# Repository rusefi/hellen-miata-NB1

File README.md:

# Hellen NB1 Miata

Issues are tracked publicly at https://github.com/rusefi/hellen-NB1-issues

[User Documentation](https://github.com/rusefi/rusefi/wiki/Hellen-NB1)

https://docs.google.com/spreadsheets/d/19Mc_QA4MTJAY1hUR4UMexbdGiqNpH4JARKxWm1VD5KA

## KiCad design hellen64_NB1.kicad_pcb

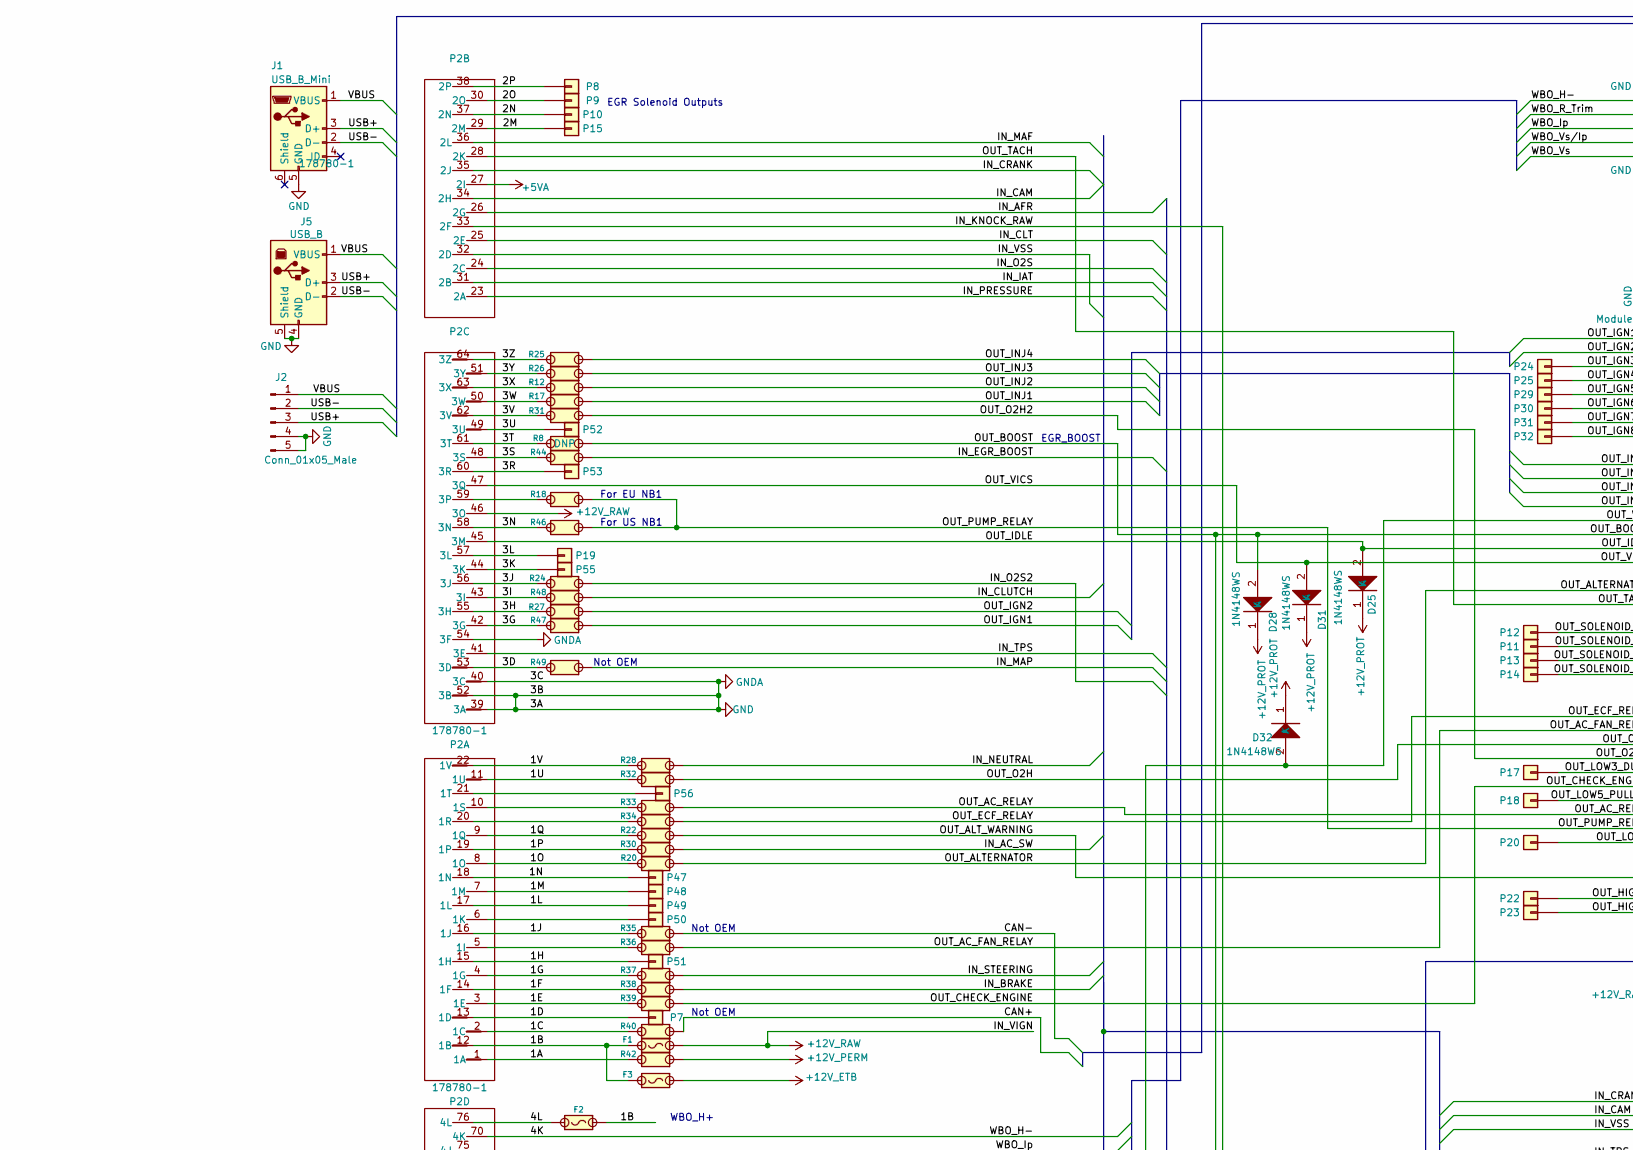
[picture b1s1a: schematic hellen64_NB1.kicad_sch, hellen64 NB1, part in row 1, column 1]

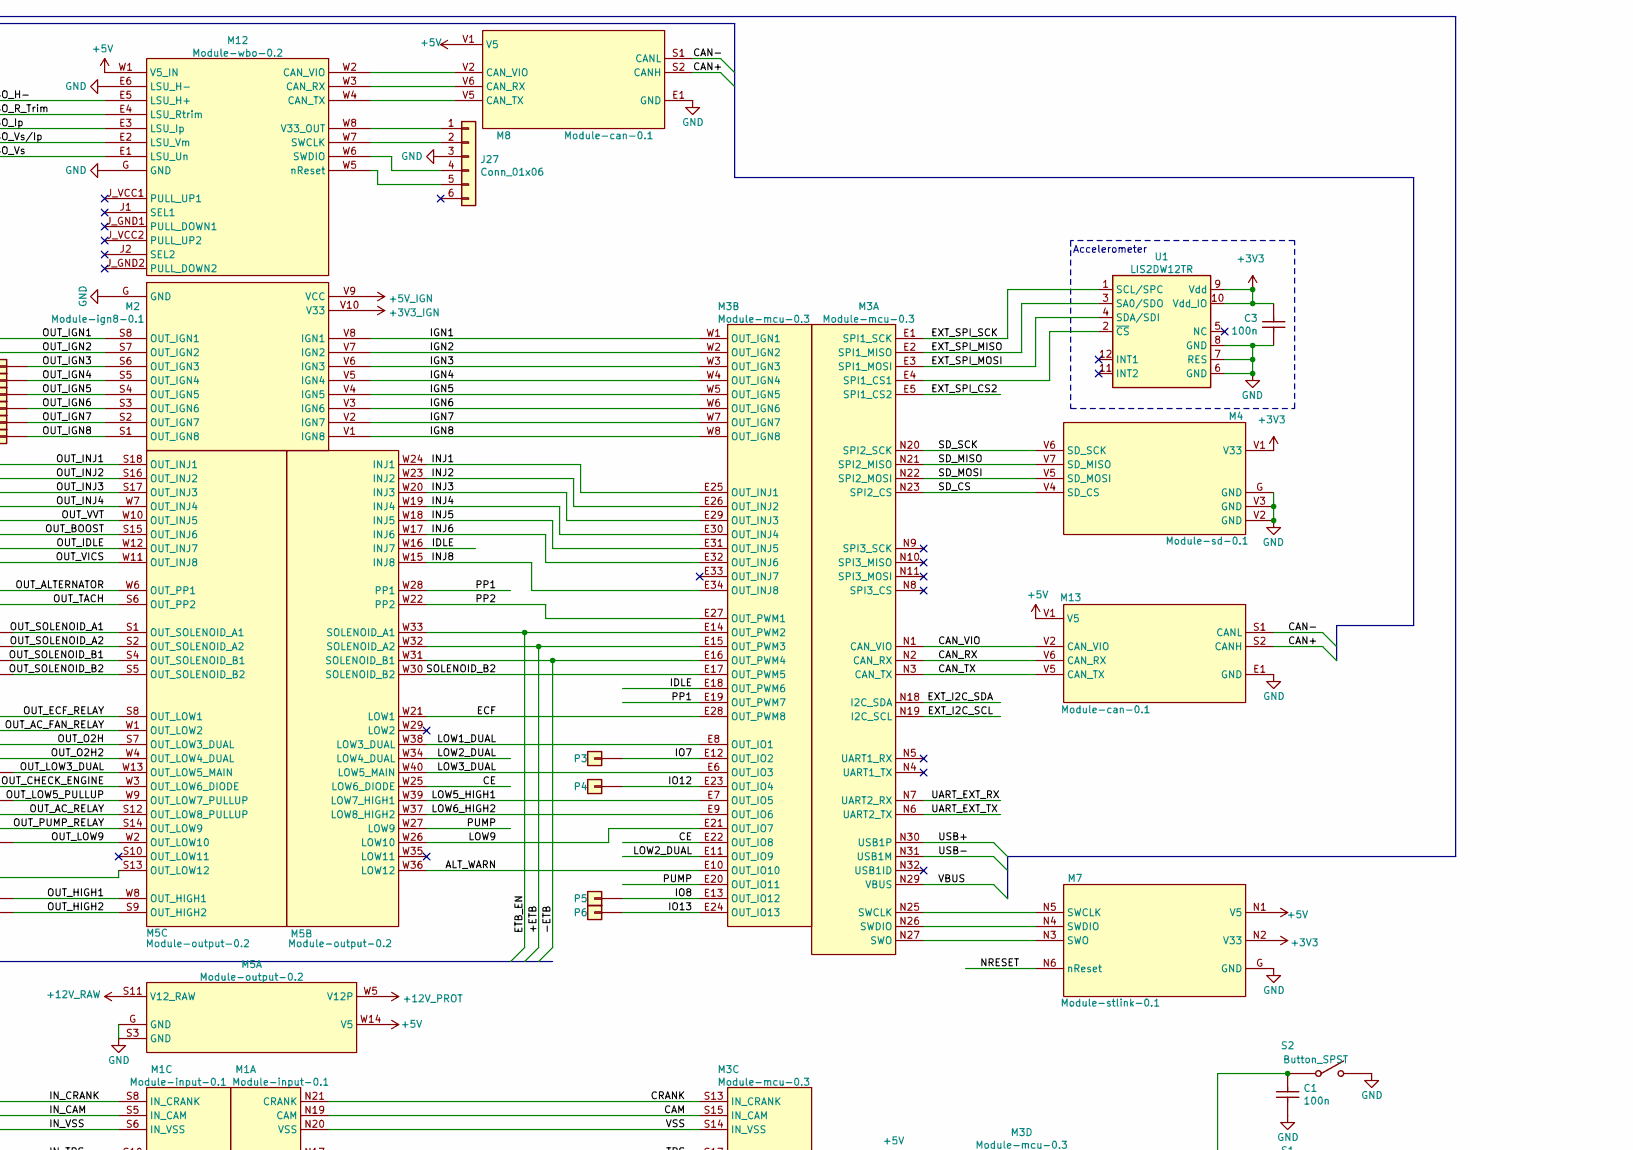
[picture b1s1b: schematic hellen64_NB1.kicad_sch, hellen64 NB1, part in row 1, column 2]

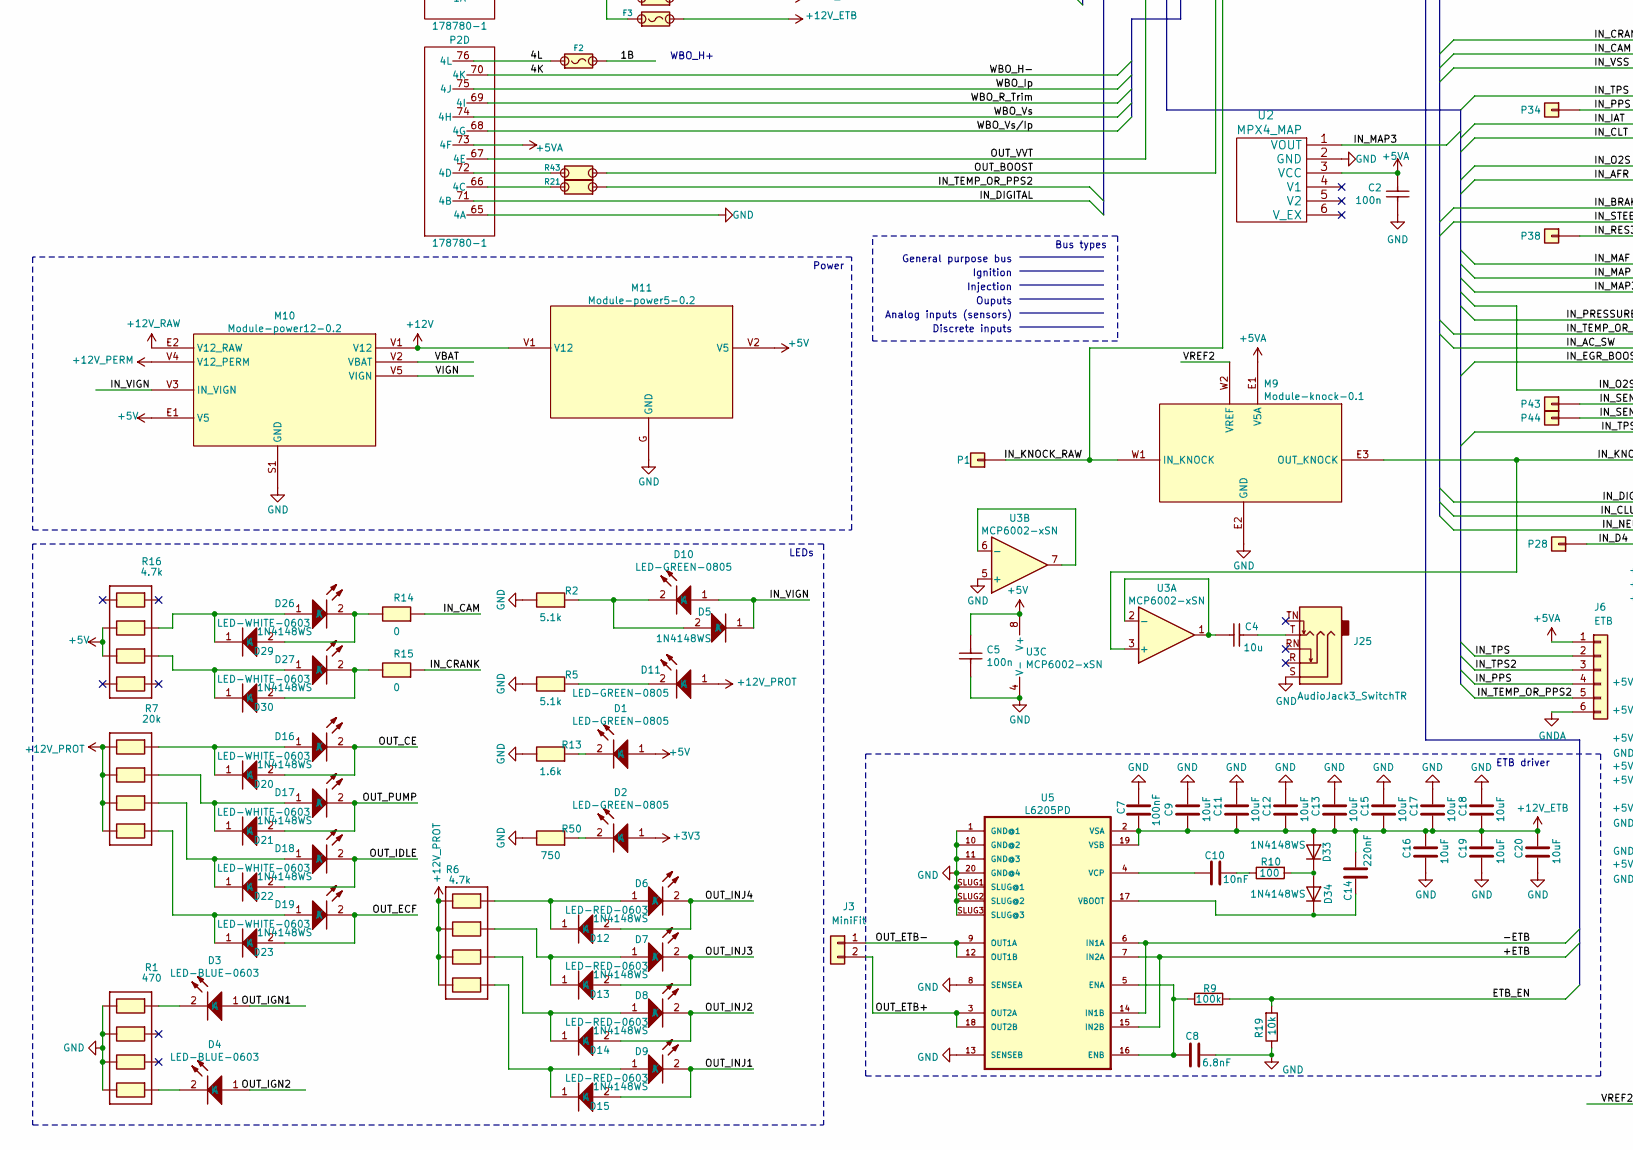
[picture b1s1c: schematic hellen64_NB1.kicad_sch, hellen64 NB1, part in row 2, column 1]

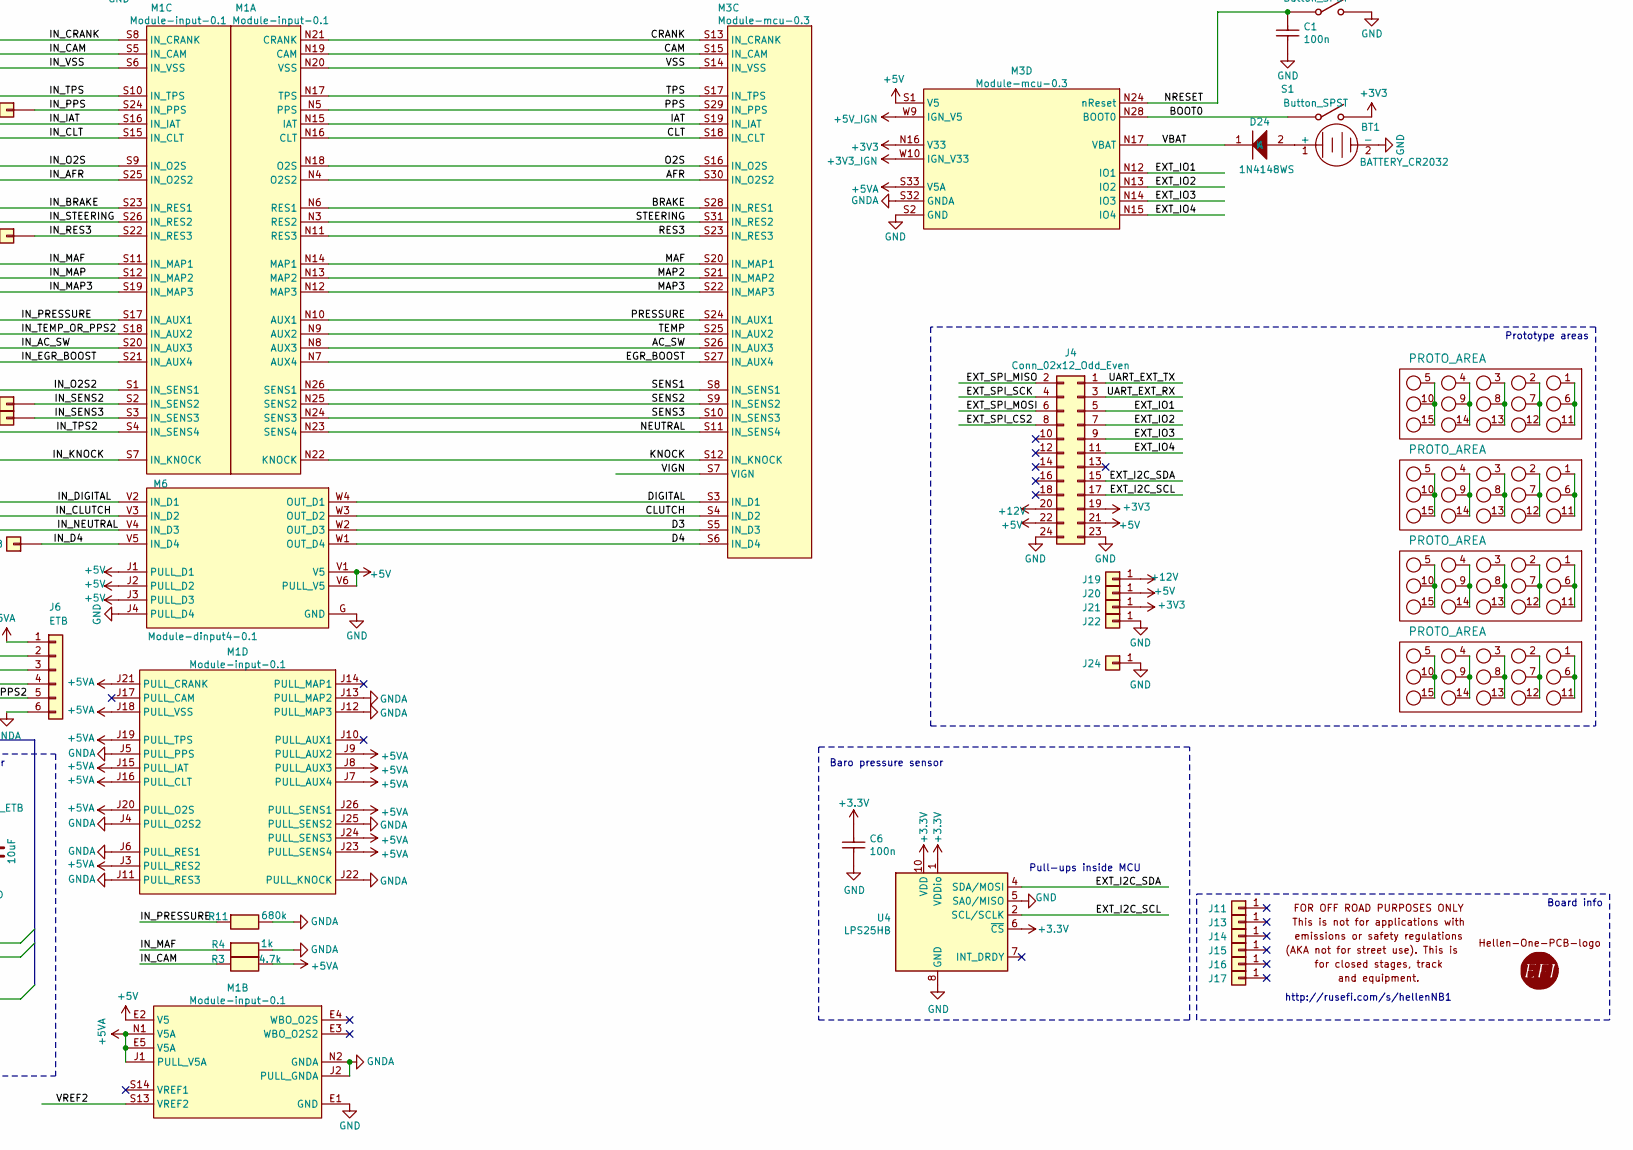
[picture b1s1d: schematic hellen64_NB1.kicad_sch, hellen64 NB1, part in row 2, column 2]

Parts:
BT1: BATTERY_CR2032; BatteryHolder_Keystone_1060_1x2032; LCSC C70377
C1, C2, C3, C5, C6: 100n; C0603; LCSC C14663
C4: 10u; C0603; LCSC C19702
C7: 100nF; C0603; LCSC C14663
C8: 6.8nF; C0603; LCSC C1631
C9, C11, C12, C13, C15, C16, C17, C18, C19, C20: 10uF; C0805; LCSC C15850
C10: 10nF; C0603; LCSC C57112
C14: 220nF; C0603; LCSC C21120
D1, D2, D10, D11: LED-GREEN-0805; LED-0805; LCSC C2297
D3, D4: LED-BLUE-0603; LED-0603; LCSC C72041
D5, D12, D13, D14, D15, D20, D21, D22, D23, D24, D25, D28, D29, D30, D31, D32, D33, D34: 1N4148WS; SOD-323; LCSC C2128
D6, D7, D8, D9: LED-RED-0603; LED-0603; LCSC C2286
D16, D17, D18, D19, D26, D27: LED-WHITE-0603; LED-0603; LCSC C2290
F1, F2, F3: Fuse-Pad-Pad; PAD-1206-PAD; LCSC C182446
G1, G3: LOGO
G2: DISCLAIMER; Off_Road_Disclaimer
G4, G5, G6, G7: PROTO_AREA
J1: USB_B_Mini; USB-MINI-B-VERTICAL; LCSC C13453
J2: Conn_01x05_Male; Molex_SPOX_5267-05A_1x05_P2.50mm_Vertical
J3: MiniFit; Molex-39301020; LCSC C240832
J4: Conn_02x12_Odd_Even; PinHeader_2x12_P2.54mm_Vertical
J5: USB_B; LCSC C46392
J6: ETB; PinHeader_1x06_P2.54mm_Vertical; LCSC C343639
J11, J13, J14, J15, J16, J17: Conn_01x01; MountingHole_4.5mm_Pad
J19, J20, J21, J22, J24: Conn_01x01; TestPoint_Pad_D2.0mm
J25: AudioJack3_SwitchTR; Jack_3.5mm_PJ-3250-5A; LCSC C165947
J27: Conn_01x06; PinHeader_1x06_P2.54mm_Vertical
M1: Module-input-0.1; input
M2: Module-ign8-0.1; ign8
M3: Module-mcu-0.3; mcu
M4: Module-sd-0.1; sd
M5: Module-output-0.2; output
M6: Module-dinput4-0.1; dinput4
M7: Module-stlink-0.1; stlink
M8, M13: Module-can-0.1; can
M9: Module-knock-0.1; knock
M10: Module-power12-0.2; power12
M11: Module-power5-0.2; power5
M12: Module-wbo-0.2; wbo
P1, P3, P4, P5, P6, P7, P8, P9, P10, P11, P12, P13, P14, P15, P17, P18, P19, P20, P22, P23, P24, P25, P28, P29, P30, P31, P32, P34, P38, P43, P44, P47, P48, P49, P50, P51, P52, P53, P55, P56: Pad; PAD-TH
P2: 178780-1
R1: 470; R0603-4; LCSC C25510
R2, R5: 5.1k; R0603; LCSC C23186
R3: 4.7k; R0603; LCSC C23162
R4: 1k; R0603; LCSC C21190
R6, R16: 4.7k; R0603-4; LCSC C1980
R7: 20k; R0603-4; LCSC C12004
R8: Jumper-Pad-Pad; PAD-0805-PAD
R9: 100k; R0603; LCSC C25803
R10: 100; R0603; LCSC C22775
R11: 680k; R0603; LCSC C25822
R12, R17, R18, R20, R21, R22, R24, R25, R26, R27, R28, R30, R31, R32, R33, R34, R35, R36, R37, R38, R39, R40, R42, R43, R44, R46, R47, R48, R49: Jumper-Pad-Pad; PAD-0805-PAD; LCSC C17477
R13: 1.6k; R0603; LCSC C22847
R14, R15: 0; R0603; LCSC C21189
R19: 10k; R0603; LCSC C25804
R50: 750; R0603; LCSC C23241
S1, S2: Button_SPST; SMD-2_2.9x3.9x1.7; LCSC C115357
U1: LIS2DW12TR; LGA-12_2x2mm_P0.5mm; LCSC C189624
U2: MPX4_MAP; MPX-4_MAP
U3: MCP6002-xSN; SOIC-8_3.9x4.9mm_P1.27mm; LCSC C7377
U4: LPS25HB; ST_HLGA-10_2.5x2.5mm_P0.6mm_LayoutBorder3x2y; LCSC C87898
U5: L6205PD; SO20POWER; LCSC C36543

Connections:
+3V3_IGN: M2.V10 (V33), M3.W10 (IGN_V33)
+5V: C5.2, D1.1 (A), J4.21, J4.22, J20.1, M1.E2 (V5), M3.S1 (V5), M5.W14 (V5), M6.J1 (PULL_D1), M6.J2 (PULL_D2), M6.J3 (PULL_D3), M6.V1 (V5), M6.V6 (PULL_V5), M7.N1 (V5), M8.V1 (V5), M10.E1 (V5), M11.V2 (V5), M12.W1 (V5_IN), M13.V1 (V5), R16.2, R16.3, U3.8 (V+)
+5VA: C2.2, J6.1, M1.E5 (V5A), M1.J1 (PULL_V5A), M1.J3 (PULL_RES2), M1.J7 (PULL_AUX4), M1.J8 (PULL_AUX3), M1.J9 (PULL_AUX2), M1.J15 (PULL_IAT), M1.J16 (PULL_CLT), M1.J18 (PULL_VSS), M1.J19 (PULL_TPS), M1.J20 (PULL_O2S), M1.J21 (PULL_CRANK), M1.J23 (PULL_SENS4), M1.J24 (PULL_SENS3), M1.J26 (PULL_SENS1), M1.N1 (V5A), M3.S33 (V5A), M9.E1 (V5A), P2.27 (2I), P2.73 (4F), R3.1, U2.3 (VCC)
+5V_IGN: M2.V9 (VCC), M3.W9 (IGN_V5)
+12V: J4.20, J19.1, M10.V1 (V12), M11.V1 (V12)
+12V_ETB: C7.2, C9.1, C11.1, C12.1, C13.1, C14.1, C15.1, C16.2, C17.1, C18.1, C19.2, C20.2, D33.2 (A), F3.2, U5.2 (VSA), U5.19 (VSB)
+12V_PERM: M10.V4 (V12_PERM), R42.1
+12V_PROT: D11.1 (A), D25.1 (K), D28.1 (K), D31.1 (K), D32.1 (K), M5.W5 (V12P), R6.1, R6.2, R6.3, R6.4, R7.1, R7.2, R7.3, R7.4
+12V_RAW: D5.1 (K), D10.1 (A), F1.2, M5.S11 (V12_RAW), M10.E2 (V12_RAW), M10.V3 (IN_VIGN), P2.46 (3O)
/1A: P2.1 (1A), R42.2
/1B: F1.1, F2.2, F3.1, P2.12 (1B)
/1C: P2.2 (1C), R40.2
/1D: P2.13 (1D), P7.1
/1E: P2.3 (1E), R39.2
/1F: P2.14 (1F), R38.2
/1G: P2.4 (1G), R37.2
/1H: P2.15 (1H), P51.1
/1J: P2.16 (1J), R35.2
/1L: P2.17 (1L), P49.1
/1M: P2.7 (1M), P48.1
/1N: P2.18 (1N), P47.1
/1O: P2.8 (1O), R20.2
/1P: P2.19 (1P), R30.2
/1Q: P2.9 (1Q), R22.2
/1U: P2.11 (1U), R32.2
/1V: P2.22 (1V), R28.2
/2M: P2.29 (2M), P15.1
/2N: P2.37 (2N), P10.1
/2O: P2.30 (2O), P9.1
/2P: P2.38 (2P), P8.1
/3D: P2.53 (3D), R49.2
/3G: P2.42 (3G), R47.2
/3H: P2.55 (3H), R27.1
/3I: P2.43 (3I), R48.2
/3J: P2.56 (3J), R24.2
/3K: P2.44 (3K), P55.1
/3L: P2.57 (3L), P19.1
/3N: P2.58 (3N), R46.2
/3R: P2.60 (3R), P53.1
/3S: P2.48 (3S), R44.2
/3T: P2.61 (3T), R8.2
/3U: P2.49 (3U), P52.1
/3V: P2.62 (3V), R31.2
/3W: P2.50 (3W), R17.1
/3X: P2.63 (3X), R12.1
/3Y: P2.51 (3Y), R26.2
/3Z: P2.64 (3Z), R25.2
/4K: M12.E5 (LSU_H+), P2.70 (4K)
/4L: F2.1, P2.76 (4L)
/+ETB: M3.E15 (OUT_PWM3), M5.W32 (SOLENOID_A2), U5.7 (IN2A), U5.15 (IN2B)
/-ETB: M3.E16 (OUT_PWM4), M5.W31 (SOLENOID_B1), U5.6 (IN1A), U5.14 (IN1B)
/AC_SW: M1.N8 (AUX3), M3.S26 (IN_AUX3)
/AFR: M1.N4 (O2S2), M3.S30 (IN_O2S2)
/ALT_WARN: M3.E10 (OUT_IO10), M5.W36 (LOW12)
/BOOT0: M3.N28 (BOOT0), S1.1
/BRAKE: M1.N6 (RES1), M3.S28 (IN_RES1)
/CAM: M1.N19 (CAM), M3.S15 (IN_CAM)
/CAN+: M8.S2 (CANH), M13.S2 (CANH), R40.1
/CAN-: M8.S1 (CANL), M13.S1 (CANL), R35.1
/CAN_RX: M3.N2 (CAN_RX), M13.V6 (CAN_RX)
/CAN_TX: M3.N3 (CAN_TX), M13.V5 (CAN_TX)
/CAN_VIO: M3.N1 (CAN_VIO), M13.V2 (CAN_VIO)
/CE: M3.E22 (OUT_IO8), M5.W25 (LOW6_DIODE)
/CLT: M1.N16 (CLT), M3.S18 (IN_CLT)
/CLUTCH: M3.S4 (IN_D2), M6.W3 (OUT_D2)
/CRANK: M1.N21 (CRANK), M3.S13 (IN_CRANK)
/D3: M3.S5 (IN_D3), M6.W2 (OUT_D3)
/D4: M3.S6 (IN_D4), M6.W1 (OUT_D4)
/DIGITAL: M3.S3 (IN_D1), M6.W4 (OUT_D1)
/ECF: M3.E28 (OUT_PWM8), M5.W21 (LOW1)
/EGR_BOOST: M1.N7 (AUX4), M3.S27 (IN_AUX4)
/ETB_EN: M3.E14 (OUT_PWM2), M5.W33 (SOLENOID_A1), R9.2, R19.2
/EXT_I2C_SCL: J4.17, M3.N19 (I2C_SCL), U4.2 (SCL/SCLK)
/EXT_I2C_SDA: J4.15, M3.N18 (I2C_SDA), U4.4 (SDA/MOSI)
/EXT_IO1: J4.5, M3.N12 (IO1)
/EXT_IO2: J4.7, M3.N13 (IO2)
/EXT_IO3: J4.9, M3.N14 (IO3)
/EXT_IO4: J4.11, M3.N15 (IO4)
/EXT_SPI_CS2: J4.8, M3.E5 (SPI1_CS2)
/EXT_SPI_MISO: J4.2, M3.E2 (SPI1_MISO), U1.3 (SA0/SDO)
/EXT_SPI_MOSI: J4.6, M3.E3 (SPI1_MOSI), U1.4 (SDA/SDI)
/EXT_SPI_SCK: J4.4, M3.E1 (SPI1_SCK), U1.1 (SCL/SPC)
/IAT: M1.N15 (IAT), M3.S19 (IN_IAT)
/IDLE: M3.E18 (OUT_PWM6), M5.W16 (INJ7)
/IGN1: M2.V8 (IGN1), M3.W1 (OUT_IGN1)
/IGN2: M2.V7 (IGN2), M3.W2 (OUT_IGN2)
/IGN3: M2.V6 (IGN3), M3.W3 (OUT_IGN3)
/IGN4: M2.V5 (IGN4), M3.W4 (OUT_IGN4)
/IGN5: M2.V4 (IGN5), M3.W5 (OUT_IGN5)
/IGN6: M2.V3 (IGN6), M3.W6 (OUT_IGN6)
/IGN7: M2.V2 (IGN7), M3.W7 (OUT_IGN7)
/IGN8: M2.V1 (IGN8), M3.W8 (OUT_IGN8)
/INJ1: M3.E25 (OUT_INJ1), M5.W24 (INJ1)
/INJ2: M3.E26 (OUT_INJ2), M5.W23 (INJ2)
/INJ3: M3.E29 (OUT_INJ3), M5.W20 (INJ3)
/INJ4: M3.E30 (OUT_INJ4), M5.W19 (INJ4)
/INJ5: M3.E31 (OUT_INJ5), M5.W18 (INJ5)
/INJ6: M3.E32 (OUT_INJ6), M5.W17 (INJ6)
/INJ8: M3.E34 (OUT_INJ8), M5.W15 (INJ8)
/IN_AC_SW: M1.S20 (IN_AUX3), R30.1
/IN_AFR: M1.S25 (IN_O2S2), P2.26 (2G)
/IN_BRAKE: M1.S23 (IN_RES1), R38.1
/IN_CAM: M1.S5 (IN_CAM), P2.34 (2H), R3.2, R14.1
/IN_CLT: M1.S15 (IN_CLT), P2.25 (2E)
/IN_CLUTCH: M6.V3 (IN_D2), R48.1
/IN_CRANK: M1.S8 (IN_CRANK), P2.35 (2J), R15.1
/IN_D4: M6.V5 (IN_D4), P28.1
/IN_DIGITAL: M6.V2 (IN_D1), P2.71 (4B)
/IN_EGR_BOOST: M1.S21 (IN_AUX4), R44.1
/IN_IAT: M1.S16 (IN_IAT), P2.31 (2B)
/IN_KNOCK: M1.S7 (IN_KNOCK), M9.E3 (OUT_KNOCK), U3.3 (+)
/IN_KNOCK_RAW: M9.W1 (IN_KNOCK), P1.1, P2.33 (2F)
/IN_MAF: M1.S11 (IN_MAP1), P2.36 (2L), R4.1
/IN_MAP: M1.S12 (IN_MAP2), R49.1
/IN_MAP3: M1.S19 (IN_MAP3), U2.1 (VOUT)
/IN_NEUTRAL: M6.V4 (IN_D3), R28.1
/IN_O2S: M1.S9 (IN_O2S), P2.24 (2C)
/IN_O2S2: M1.S1 (IN_SENS1), R24.1
/IN_PPS: J6.4, M1.S24 (IN_PPS), P34.1
/IN_PRESSURE: M1.S17 (IN_AUX1), P2.23 (2A), R11.1
/IN_RES3: M1.S22 (IN_RES3), P38.1
/IN_SENS2: M1.S2 (IN_SENS2), P43.1
/IN_SENS3: M1.S3 (IN_SENS3), P44.1
/IN_STEERING: M1.S26 (IN_RES2), R37.1
/IN_TEMP_OR_PPS2: J6.5, M1.S18 (IN_AUX2), R21.1
/IN_TPS: J6.2, M1.S10 (IN_TPS), P2.41 (3E)
/IN_TPS2: J6.3, M1.S4 (IN_SENS4)
/IN_VSS: M1.S6 (IN_VSS), P2.32 (2D)
/IO7: M3.E12 (OUT_IO2), P3.1
/IO8: M3.E13 (OUT_IO12), P5.1
/IO12: M3.E23 (OUT_IO4), P4.1
/IO13: M3.E24 (OUT_IO13), P6.1
/KNOCK: M1.N22 (KNOCK), M3.S12 (IN_KNOCK)
/LOW1_DUAL: M3.E8 (OUT_IO1), M5.W38 (LOW3_DUAL)
/LOW2_DUAL: M3.E11 (OUT_IO9), M5.W34 (LOW4_DUAL)
/LOW3_DUAL: M3.E6 (OUT_IO3), M5.W40 (LOW5_MAIN)
/LOW5_HIGH1: M3.E7 (OUT_IO5), M5.W39 (LOW7_HIGH1)
/LOW6_HIGH2: M3.E9 (OUT_IO6), M5.W37 (LOW8_HIGH2)
/LOW9: M3.E21 (OUT_IO7), M5.W26 (LOW10)
/MAF: M1.N14 (MAP1), M3.S20 (IN_MAP1)
/MAP2: M1.N13 (MAP2), M3.S21 (IN_MAP2)
/MAP3: M1.N12 (MAP3), M3.S22 (IN_MAP3)
/NEUTRAL: M1.N23 (SENS4), M3.S11 (IN_SENS4)
/NRESET: C1.2, M3.N24 (nReset), M7.N6 (nReset), S2.1
/O2S: M1.N18 (O2S), M3.S16 (IN_O2S)
/OUT_AC_FAN_RELAY: M5.W1 (OUT_LOW2), R36.1
/OUT_AC_RELAY: M5.S12 (OUT_LOW8_PULLUP), R33.1
/OUT_ALTERNATOR: M5.W6 (OUT_PP1), R20.1
/OUT_ALT_WARNING: M5.S13 (OUT_LOW12), R22.1
/OUT_BOOST: D28.2 (A), M5.S15 (OUT_INJ6), R8.1, R43.1
/OUT_CE: D16.2 (K), D20.2 (A)
/OUT_CHECK_ENGINE: M5.W3 (OUT_LOW6_DIODE), R39.1
/OUT_ECF: D19.2 (K), D23.2 (A)
/OUT_ECF_RELAY: M5.S8 (OUT_LOW1), R34.1
/OUT_ETB+: J3.2, U5.3 (OUT2A), U5.18 (OUT2B)
/OUT_ETB-: J3.1, U5.9 (OUT1A), U5.12 (OUT1B)
/OUT_HIGH1: M5.W8 (OUT_HIGH1), P22.1
/OUT_HIGH2: M5.S9 (OUT_HIGH2), P23.1
/OUT_IDLE: D18.2 (K), D22.2 (A), D25.2 (A), M5.W12 (OUT_INJ7), P2.45 (3M)
/OUT_IGN1: D3.1 (A), M2.S8 (OUT_IGN1), R47.1
/OUT_IGN2: D4.1 (A), M2.S7 (OUT_IGN2), R27.2
/OUT_IGN3: M2.S6 (OUT_IGN3), P24.1
/OUT_IGN4: M2.S5 (OUT_IGN4), P25.1
/OUT_IGN5: M2.S4 (OUT_IGN5), P29.1
/OUT_IGN6: M2.S3 (OUT_IGN6), P30.1
/OUT_IGN7: M2.S2 (OUT_IGN7), P31.1
/OUT_IGN8: M2.S1 (OUT_IGN8), P32.1
/OUT_INJ1: D9.2 (K), D15.2 (A), M5.S18 (OUT_INJ1), R17.2
/OUT_INJ2: D8.2 (K), D14.2 (A), M5.S16 (OUT_INJ2), R12.2
/OUT_INJ3: D7.2 (K), D13.2 (A), M5.S17 (OUT_INJ3), R26.1
/OUT_INJ4: D6.2 (K), D12.2 (A), M5.W7 (OUT_INJ4), R25.1
/OUT_LOW3_DUAL: M5.W13 (OUT_LOW5_MAIN), P17.1
/OUT_LOW5_PULLUP: M5.W9 (OUT_LOW7_PULLUP), P18.1
/OUT_LOW9: M5.W2 (OUT_LOW10), P20.1
/OUT_O2H: M5.S7 (OUT_LOW3_DUAL), R32.1
/OUT_O2H2: M5.W4 (OUT_LOW4_DUAL), R31.1
/OUT_PUMP: D17.2 (K), D21.2 (A)
/OUT_PUMP_RELAY: M5.S14 (OUT_LOW9), R18.1, R46.1
/OUT_SOLENOID_A1: M5.S1 (OUT_SOLENOID_A1), P12.1
/OUT_SOLENOID_A2: M5.S2 (OUT_SOLENOID_A2), P11.1
/OUT_SOLENOID_B1: M5.S4 (OUT_SOLENOID_B1), P13.1
/OUT_SOLENOID_B2: M5.S5 (OUT_SOLENOID_B2), P14.1
/OUT_TACH: M5.S6 (OUT_PP2), P2.28 (2K)
/OUT_VICS: D31.2 (A), M5.W11 (OUT_INJ8), P2.47 (3Q)
/OUT_VVT: D32.2 (A), M5.W10 (OUT_INJ5), P2.67 (4E)
/PP1: M3.E19 (OUT_PWM7), M5.W28 (PP1)
/PP2: M3.E27 (OUT_PWM1), M5.W22 (PP2)
/PPS: M1.N5 (PPS), M3.S29 (IN_PPS)
/PRESSURE: M1.N10 (AUX1), M3.S24 (IN_AUX1)
/PUMP: M3.E20 (OUT_IO11), M5.W27 (LOW9)
/RES3: M1.N11 (RES3), M3.S23 (IN_RES3)
/SD_CS: M3.N23 (SPI2_CS), M4.V4 (SD_CS)
/SD_MISO: M3.N21 (SPI2_MISO), M4.V7 (SD_MISO)
/SD_MOSI: M3.N22 (SPI2_MOSI), M4.V5 (SD_MOSI)
/SD_SCK: M3.N20 (SPI2_SCK), M4.V6 (SD_SCK)
/SENS1: M1.N26 (SENS1), M3.S8 (IN_SENS1)
/SENS2: M1.N25 (SENS2), M3.S9 (IN_SENS2)
/SENS3: M1.N24 (SENS3), M3.S10 (IN_SENS3)
/SOLENOID_B2: M3.E17 (OUT_PWM5), M5.W30 (SOLENOID_B2)
/STEERING: M1.N3 (RES2), M3.S31 (IN_RES2)
/TEMP: M1.N9 (AUX2), M3.S25 (IN_AUX2)
/TPS: M1.N17 (TPS), M3.S17 (IN_TPS)
/UART_EXT_RX: J4.3, M3.N7 (UART2_RX)
/UART_EXT_TX: J4.1, M3.N6 (UART2_TX)
/USB+: J1.3 (D+), J2.3, J5.3 (D+), M3.N30 (USB1P)
/USB-: J1.2 (D-), J2.2, J5.2 (D-), M3.N31 (USB1M)
/VBAT: D24.1 (K), M3.N17 (VBAT), M10.V2 (VBAT)
/VBUS: J1.1 (VBUS), J2.1, J5.1 (VBUS), M3.N29 (VBUS)
/VIGN: M3.S7 (VIGN), M10.V5 (VIGN)
/VREF2: M1.S13 (VREF2), M9.W2 (VREF)
/VSS: M1.N20 (VSS), M3.S14 (IN_VSS)
/WBO_Ip: M12.E3 (LSU_Ip), P2.75 (4J)
/WBO_R_Trim: M12.E4 (LSU_Rtrim), P2.69 (4I)
/WBO_Vs: M12.E1 (LSU_Un), P2.74 (4H)
/WBO_Vs/Ip: M12.E2 (LSU_Vm), P2.68 (4G)
GND: BT1.2 (-), C1.1, C2.1, C3.1, C5.1, C6.1, C7.1, C8.2, C9.2, C11.2, C12.2, C13.2, C15.2, C16.1, C17.2, C18.2, C19.1, C20.1, J1.5 (GND), J2.4, J2.5, J4.23, J4.24, J5.4 (GND), J5.5 (Shield), J6.6, J22.1, J24.1, J25.S, J27.3, M1.E1 (GND), M1.J2 (PULL_GNDA), M1.J4 (PULL_O2S2), M1.J5 (PULL_PPS), M1.J6 (PULL_RES1), M1.J11 (PULL_RES3), M1.J12 (PULL_MAP3), M1.J13 (PULL_MAP2), M1.J22 (PULL_KNOCK), M1.J25 (PULL_SENS2), M1.N2 (GNDA), M2.G (GND), M3.S2 (GND), M3.S32 (GNDA), M4.G (GND), M4.V2 (GND), M4.V3 (GND), M5.G (GND), M5.S3 (GND), M6.G (GND), M6.J4 (PULL_D4), M7.G (GND), M8.E1 (GND), M9.E2 (GND), M10.S1 (GND), M11.G (GND), M12.E6 (LSU_H-), M12.G (GND), M13.E1 (GND), P2.39 (3A), P2.40 (3C), P2.52 (3B), P2.54 (3F), P2.65 (4A), R1.1, R1.2, R1.3, R1.4, R2.2, R4.2, R5.2, R11.2, R13.2, R19.1, R50.2, S2.2, U1.6 (GND), U1.7 (RES), U1.8 (GND), U2.2 (GND), U3.4 (V-), U3.5 (+), U4.3 (GND), U4.5 (SA0/MISO), U4.8 (GND), U4.9 (GND), U5.1 (GND@1), U5.8 (SENSEA), U5.10 (GND@2), U5.11 (GND@3), U5.13 (SENSEB), U5.20 (GND@4), U5.SLUG1 (SLUG@1), U5.SLUG2 (SLUG@2), U5.SLUG3 (SLUG@3)
unnamed: BT1.1 (+), D24.2 (A)
unnamed: C4.1, J25.T
unnamed: C4.2, U3.1, U3.2 (-)
unnamed: C8.1, R9.1, U5.5 (ENA), U5.16 (ENB)
unnamed: C10.1, R10.1
unnamed: C10.2, U5.4 (VCP)
unnamed: C14.2, D34.1 (K), U5.17 (VBOOT)
unnamed: D1.2 (K), R13.1
unnamed: D2.2 (K), R50.1
unnamed: D3.2 (K), R1.8
unnamed: D4.2 (K), R1.5
unnamed: D5.2 (A), D10.2 (K), R2.1
unnamed: D11.2 (K), R5.1
unnamed: D6.1 (A), D12.1 (K), R6.8
unnamed: D7.1 (A), D13.1 (K), R6.7
unnamed: D8.1 (A), D14.1 (K), R6.6
unnamed: D9.1 (A), D15.1 (K), R6.5
unnamed: D16.1 (A), D20.1 (K), R7.8
unnamed: D17.1 (A), D21.1 (K), R7.7
unnamed: D18.1 (A), D22.1 (K), R7.6
unnamed: D19.1 (A), D23.1 (K), R7.5
unnamed: D26.1 (A), D29.1 (K), R16.7
unnamed: D26.2 (K), D29.2 (A), R14.2
unnamed: D27.1 (A), D30.1 (K), R16.6
unnamed: D27.2 (K), D30.2 (A), R15.2
unnamed: D33.1 (K), D34.2 (A), R10.2
unnamed: G4.1, G4.6, G4.11
unnamed: G4.5, G4.10, G4.15
unnamed: G4.2, G4.7, G4.12
unnamed: G4.3, G4.8, G4.13
unnamed: G4.4, G4.9, G4.14
unnamed: G5.1, G5.6, G5.11
unnamed: G5.5, G5.10, G5.15
unnamed: G5.2, G5.7, G5.12
unnamed: G5.3, G5.8, G5.13
unnamed: G5.4, G5.9, G5.14
unnamed: G6.1, G6.6, G6.11
unnamed: G6.5, G6.10, G6.15
unnamed: G6.2, G6.7, G6.12
unnamed: G6.3, G6.8, G6.13
unnamed: G6.4, G6.9, G6.14
unnamed: G7.1, G7.6, G7.11
unnamed: G7.5, G7.10, G7.15
unnamed: G7.2, G7.7, G7.12
unnamed: G7.3, G7.8, G7.13
unnamed: G7.4, G7.9, G7.14
unnamed: J27.1, M12.W8 (V33_OUT)
unnamed: J27.2, M12.W7 (SWCLK)
unnamed: J27.4, M12.W6 (SWDIO)
unnamed: J27.5, M12.W5 (nReset)
unnamed: M3.E4 (SPI1_CS1), U1.2 (~CS)
unnamed: M3.N25 (SWCLK), M7.N5 (SWCLK)
unnamed: M3.N26 (SWDIO), M7.N4 (SWDIO)
unnamed: M3.N27 (SWO), M7.N3 (SWO)
unnamed: M8.V2 (CAN_VIO), M12.W2 (CAN_VIO)
unnamed: M8.V6 (CAN_RX), M12.W3 (CAN_RX)
unnamed: M8.V5 (CAN_TX), M12.W4 (CAN_TX)
unnamed: P2.5 (1I), R36.2
unnamed: P2.6 (1K), P50.1
unnamed: P2.10 (1S), R33.2
unnamed: P2.20 (1R), R34.2
unnamed: P2.21 (1T), P56.1
unnamed: P2.59 (3P), R18.2
unnamed: P2.66 (4C), R21.2
unnamed: P2.72 (4D), R43.2
unnamed: U3.6 (-), U3.7

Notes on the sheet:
Not OEM
For EU NB1
For US NB1
EGR Solenoid Outputs
WBO_H+
LEDs
Power
General purpose bus
Ignition
Injection
Ouputs
Analog inputs (sensors)
Discrete inputs
EGR_BOOST
Bus types
ETB driver
Baro pressure sensor
Pull-ups inside MCU
Accelerometer
http://rusefi.com/s/hellenNB1
Prototype areas
Board info

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
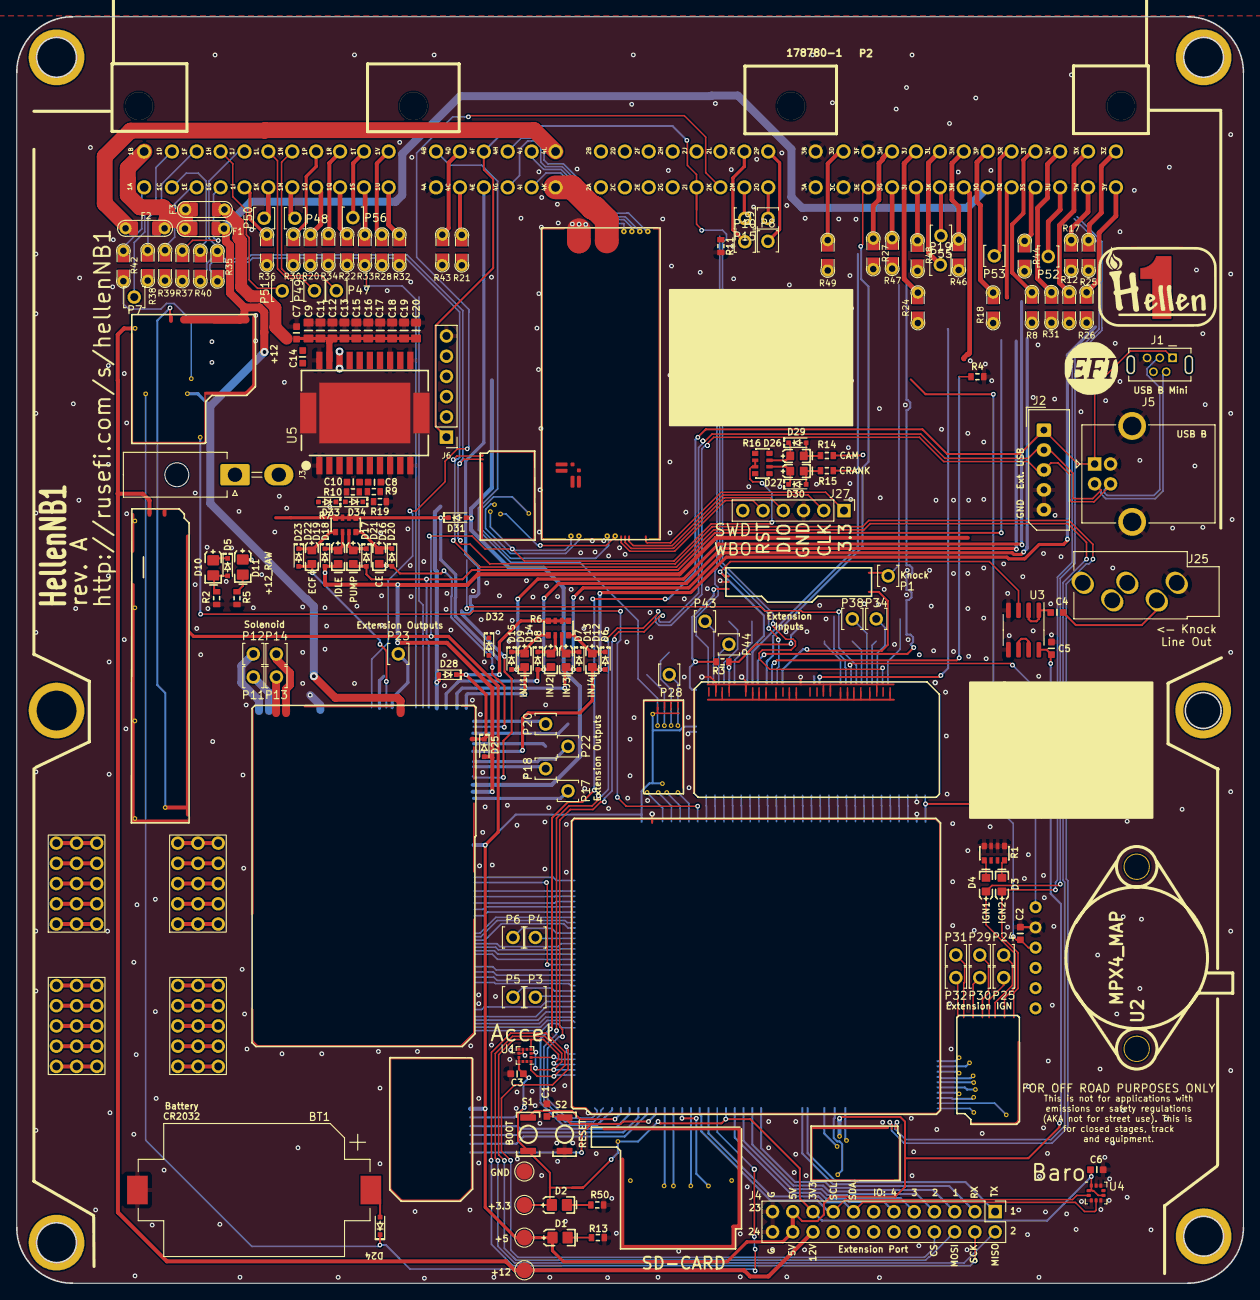
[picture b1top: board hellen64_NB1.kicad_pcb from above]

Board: 2 copper layers, 154.0 x 159.0 mm, 191 parts (1 on the bottom side), 283 nets.

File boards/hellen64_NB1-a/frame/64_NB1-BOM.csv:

Comment,Designator,Footprint,LCSC Part #
"BATTERY_CR2032","BT1","BATTERY-2032","C70377"
"100n","C1","C0603","C14663"
"100n","C2","C0603","C14663"
"100n","C3","C0603","C14663"
"10u","C4","C0603","C19702"
"100n","C5","C0603","C14663"
"100n","C6","C0603","C14663"
"100n","C7","C0603","C14663"
"6.8n","C8","C0603","C1631"
"10u","C9","C0805","C15850"
"10n","C10","C0603","C57112"
"10u","C11","C0805","C15850"
"10u","C12","C0805","C15850"
"10u","C13","C0805","C15850"
"220n","C14","C0603","C21120"
"10u","C15","C0805","C15850"
"10u","C16","C0805","C15850"
"10u","C17","C0805","C15850"
"10u","C18","C0805","C15850"
"10u","C19","C0805","C15850"
"10u","C20","C0805","C15850"
"LED-GREEN-0805","D1","LED-0805","C2297"
"LED-GREEN-0805","D2","LED-0805","C2297"
"LED-BLUE-0603","D3","LED-0603","C72041"
"LED-BLUE-0603","D4","LED-0603","C72041"
"1N4148WS","D5","SOD-323","C2128"
"LED-RED-0603","D6","LED-0603","C2286"
"LED-RED-0603","D7","LED-0603","C2286"
"LED-RED-0603","D8","LED-0603","C2286"
"LED-RED-0603","D9","LED-0603","C2286"
"LED-GREEN-0805","D10","LED-0805","C2297"
"LED-GREEN-0805","D11","LED-0805","C2297"
"1N4148WS","D12","SOD-323","C2128"
"1N4148WS","D13","SOD-323","C2128"
"1N4148WS","D14","SOD-323","C2128"
"1N4148WS","D15","SOD-323","C2128"
"LED-WHITE-0603","D16","LED-0603","C2290"
"LED-WHITE-0603","D17","LED-0603","C2290"
"LED-WHITE-0603","D18","LED-0603","C2290"
"LED-WHITE-0603","D19","LED-0603","C2290"
"1N4148WS","D20","SOD-323","C2128"
"1N4148WS","D21","SOD-323","C2128"
"1N4148WS","D22","SOD-323","C2128"
"1N4148WS","D23","SOD-323","C2128"
"1N4148WS","D24","SOD-323","C2128"
"B5819W","D25","SOD-123","C8598"
"LED-WHITE-0603","D26","LED-0603","C2290"
"LED-WHITE-0603","D27","LED-0603","C2290"
"B5819W","D28","SOD-123","C8598"
"1N4148WS","D29","SOD-323","C2128"
"1N4148WS","D30","SOD-323","C2128"
"B5819W","D31","SOD-123","C8598"
"B5819W","D32","SOD-123","C8598"
"1N4148WS","D33","SOD-323","C2128"
"1N4148WS","D34","SOD-323","C2128"
"Fuse-Pad-Pad","F1","PAD-1206-PAD","C182446"
"Fuse-Pad-Pad","F2","PAD-1206-PAD","C182446"
"Fuse-Pad-Pad","F3","PAD-1206-PAD","C182446"
"LOGO","G1","LOGO",""
"DISCLAIMER","G2","Off_Road_Disclaimer",""
"LOGO","G3","LOGO",""
"PROTO_AREA","G4","PROTO_AREA",""
"PROTO_AREA","G5","PROTO_AREA",""
"PROTO_AREA","G6","PROTO_AREA",""
"PROTO_AREA","G7","PROTO_AREA",""
"PROTO_AREA","G9","PROTO_AREA",""
"PROTO_AREA","G11","PROTO_AREA",""
"PROTO_AREA","G12","PROTO_AREA",""
"USB_B_Mini","J1","USB-MINI-B-VERTICAL","C13453"
"Conn_01x05_Male","J2","Molex_SPOX_5267-05A_1x05_P2.50mm_Vertical",""
"MiniFit","J3","Molex-39301020","C240832"
"Conn_02x12_Odd_Even","J4","PinHeader_2x12_P2.54mm_Vertical",""
"USB_B","J5","USB_B","C46392"
"ETB","J6","PinHeader_1x06_P2.54mm_Vertical","C343639"
"Conn_01x01","J11","MountingHole_4.5mm_Pad",""
"Conn_01x01","J13","MountingHole_4.5mm_Pad",""
"Conn_01x01","J14","MountingHole_4.5mm_Pad",""
"Conn_01x01","J15","MountingHole_4.5mm_Pad",""
"Conn_01x01","J16","MountingHole_4.5mm_Pad",""
"Conn_01x01","J17","MountingHole_4.5mm_Pad",""
"Conn_01x01","J19","TestPoint_Pad_D2.0mm",""
"Conn_01x01","J20","TestPoint_Pad_D2.0mm",""
"Conn_01x01","J21","TestPoint_Pad_D2.0mm",""
"Conn_01x01","J22","TestPoint_Pad_D2.0mm",""
"Conn_01x01","J24","TestPoint_Pad_D2.0mm",""
"AudioJack3_SwitchTR","J25","Jack_3.5mm_PJ-3250-5A","C165947"
"Conn_01x06","J27","PinHeader_1x06_P2.54mm_Vertical",""
"Module:input/0.1","M1","input",""
"Module:ign8/0.1","M2","ign8",""
"Module:mcu/0.5","M3","mcu",""
"Module:sd/0.1","M4","sd",""
"Module:output/0.2","M5","output",""
"Module:dinput4/0.1","M6","dinput4",""
"Module:stlink/0.1","M7","stlink",""
"Module:can/0.1","M8","can",""
"Module:knock/0.1","M9","knock",""
"Module:power12/0.2","M10","power12",""
"Module:power5/0.2","M11","power5",""
"Module:wbo/0.2","M12","wbo",""
"Module:can/0.1","M13","can",""
"Pad","P1","PAD-TH",""
"178780-1","P2","178780-1",""
"Pad","P3","PAD-TH",""
"Pad","P4","PAD-TH",""
"Pad","P5","PAD-TH",""
"Pad","P6","PAD-TH",""
"Pad","P7","PAD-TH",""
"Pad","P8","PAD-TH",""
"Pad","P9","PAD-TH",""
"Pad","P10","PAD-TH",""
"Pad","P11","PAD-TH",""
"Pad","P12","PAD-TH",""
"Pad","P13","PAD-TH",""
"Pad","P14","PAD-TH",""
"Pad","P15","PAD-TH",""
"Pad","P17","PAD-TH",""
"Pad","P18","PAD-TH",""
"Pad","P19","PAD-TH",""
"Pad","P20","PAD-TH",""
"Pad","P22","PAD-TH",""
"Pad","P23","PAD-TH",""
"Pad","P24","PAD-TH",""
"Pad","P25","PAD-TH",""
"Pad","P28","PAD-TH",""
"Pad","P29","PAD-TH",""
"Pad","P30","PAD-TH",""
"Pad","P31","PAD-TH",""
"Pad","P32","PAD-TH",""
"Pad","P38","PAD-TH",""
"Pad","P43","PAD-TH",""
"Pad","P44","PAD-TH",""
"Pad","P47","PAD-TH",""
"Pad","P48","PAD-TH",""
"Pad","P49","PAD-TH",""
"Pad","P50","PAD-TH",""
"Pad","P51","PAD-TH",""
"Pad","P52","PAD-TH",""
"Pad","P53","PAD-TH",""
"Pad","P55","PAD-TH",""
"Pad","P56","PAD-TH",""
"470","R1","R0603-4","C25510"
"5.1k","R2","R0603","C23186"
"4.7k","R3","R0603","C23162"
"1k","R4","R0603","C21190"
"5.1k","R5","R0603","C23186"
"4.7k","R6","R0603-4","C1980"
"20k","R7","R0603-4","C12004"
"Jumper-Pad-Pad","R8","PAD-0805-PAD","C17477"
"100k","R9","R0603","C25803"
"100","R10","R0603","C22775"
"680k","R11","R0603","C25822"
"Jumper-Pad-Pad","R12","PAD-0805-PAD"," C17477"
"1.6k","R13","R0603","C22847"
"0","R14","R0603","C21189"
"0","R15","R0603","C21189"
"4.7k","R16","R0603-4","C1980"
"Jumper-Pad-Pad","R17","PAD-0805-PAD"," C17477"
"Jumper-Pad-Pad","R18","PAD-0805-PAD"," C17477"
"10k","R19","R0603","C25804"
"Jumper-Pad-Pad","R20","PAD-0805-PAD"," C17477"
"Jumper-Pad-Pad","R21","PAD-0805-PAD"," C17477"
"Jumper-Pad-Pad","R22","PAD-0805-PAD"," C17477"
"Jumper-Pad-Pad","R24","PAD-0805-PAD"," C17477"
"Jumper-Pad-Pad","R25","PAD-0805-PAD"," C17477"
"Jumper-Pad-Pad","R26","PAD-0805-PAD"," C17477"
"Jumper-Pad-Pad","R27","PAD-0805-PAD"," C17477"
"Jumper-Pad-Pad","R28","PAD-0805-PAD"," C17477"
"Jumper-Pad-Pad","R30","PAD-0805-PAD"," C17477"
"Jumper-Pad-Pad","R31","PAD-0805-PAD"," C17477"
"Jumper-Pad-Pad","R32","PAD-0805-PAD"," C17477"
"Jumper-Pad-Pad","R33","PAD-0805-PAD"," C17477"
"Jumper-Pad-Pad","R34","PAD-0805-PAD"," C17477"
"Jumper-Pad-Pad","R35","PAD-0805-PAD"," C17477"
"Jumper-Pad-Pad","R36","PAD-0805-PAD"," C17477"
"Jumper-Pad-Pad","R37","PAD-0805-PAD"," C17477"
"Jumper-Pad-Pad","R38","PAD-0805-PAD"," C17477"
"Jumper-Pad-Pad","R39","PAD-0805-PAD"," C17477"
"Jumper-Pad-Pad","R40","PAD-0805-PAD"," C17477"
"Jumper-Pad-Pad","R42","PAD-0805-PAD"," C17477"
"Jumper-Pad-Pad","R43","PAD-0805-PAD"," C17477"
"Jumper-Pad-Pad","R44","PAD-0805-PAD"," C17477"
"Jumper-Pad-Pad","R46","PAD-0805-PAD"," C17477"
"Jumper-Pad-Pad","R47","PAD-0805-PAD"," C17477"
"Jumper-Pad-Pad","R48","PAD-0805-PAD"," C17477"
"Jumper-Pad-Pad","R49","PAD-0805-PAD"," C17477"
"750","R50","R0603","C23241"
"Button_SPST","S1","SMD-2_2.9x3.9x1.7","C115357"
"Button_SPST","S2","SMD-2_2.9x3.9x1.7","C115357"
"LIS2DW12TR","U1","LGA-12_2x2mm_P0.5mm","C189624"
"MPX4_MAP","U2","MPX-4_MAP",""
"MCP6002-xSN","U3","SO8","C7377"
"LPS25HB","U4","HLGA-10","C87898"
"L6205PD","U5","SO20POWER","C36543"

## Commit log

2021-02-19 hellen-one
2021-07-01 initial kicad files
2021-07-02 new pcb board shape, dims & holes for NB1 + trying to fit components inside (remove SD-card ext.header)
2021-07-02 export the schematics draft
2021-07-10 New 178780-1 76p connector footprint & board holes
2021-07-17 update schematic
2021-08-18 update schematics - ETB
2021-09-09 pcb pre-alpha is ready
2021-09-09 https://github.com/rusefi/hellen-NB1-issues/issues/6 https://github.com/rusefi/hellen-NB1-issues/issues/7
2021-09-13 board files (rev.A first test)
2021-09-14 fix AC_FAN_RELAY
2021-09-15 JLC BOM adjustments
2021-09-23 remove fix https://github.com/rusefi/hellen-NB1-issues/issues/13
2021-10-21 fix https://github.com/rusefi/hellen-NB1-issues/issues/18
2021-11-27 etb connector 6pin->8pin
2021-11-27 board files (PARTIAL, no iBom & board-image)
2021-11-29 https://github.com/rusefi/hellen-NB1-issues/issues/25
2022-03-17 rev.C https://github.com/rusefi/hellen-NB1-issues/issues/32 https://github.com/rusefi/hellen-NB1-issues/issues/30 https://github.com/rusefi/hellen-NB1-issues/issues/28 https://github.com/rusefi/helle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
2022-03-17 rev.C gerbers
